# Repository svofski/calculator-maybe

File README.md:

# MK-61 and stuff

This is a collection of mildly cohesive projects related to Soviet programmable RPN calculator emulation, period-accurate displays and their decent modern imitations.

## ИЛЦ2-12/8Л module

[Standalone VFD Module](/vfdmodule)

## OLED imitation

SH1122 256x64 grayscale OLED is used to fake the VFD look. It's not the real thing, but pretty close.

A part of mk61, it is also available as a standalone minimal project/library: [vfd-imitator](https://github.com/svofski/vfd-imitator)

## MK-61

Based on [mk-61 project by sergev](https://github.com/sergev/mk-61) and [emu145 by fixelsan](https://github.com/fixelsan/emu145/). 

Runs on Pi Pico. Eventually wants to become a usable calculator with buttons and stuff. It will use either of the two displays above.

[Code here](/arduino/mk61vak)

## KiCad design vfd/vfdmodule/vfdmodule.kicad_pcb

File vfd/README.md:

# ILC2-12/8L driver module

 * Interface: SPI
 * 5V supply
 * VFD conroller PT6315

## Hardware

[KiCad project](/vfd/vfdmodule) 

[view in KiCanvas](https://kicanvas.org/?github=https%3A%2F%2Fgithub.com%2Fsvofski%2Fcalculator-maybe%2Ftree%2Fmaster%2Fvfd%2Fvfdmodule)

## Firmware

Soon

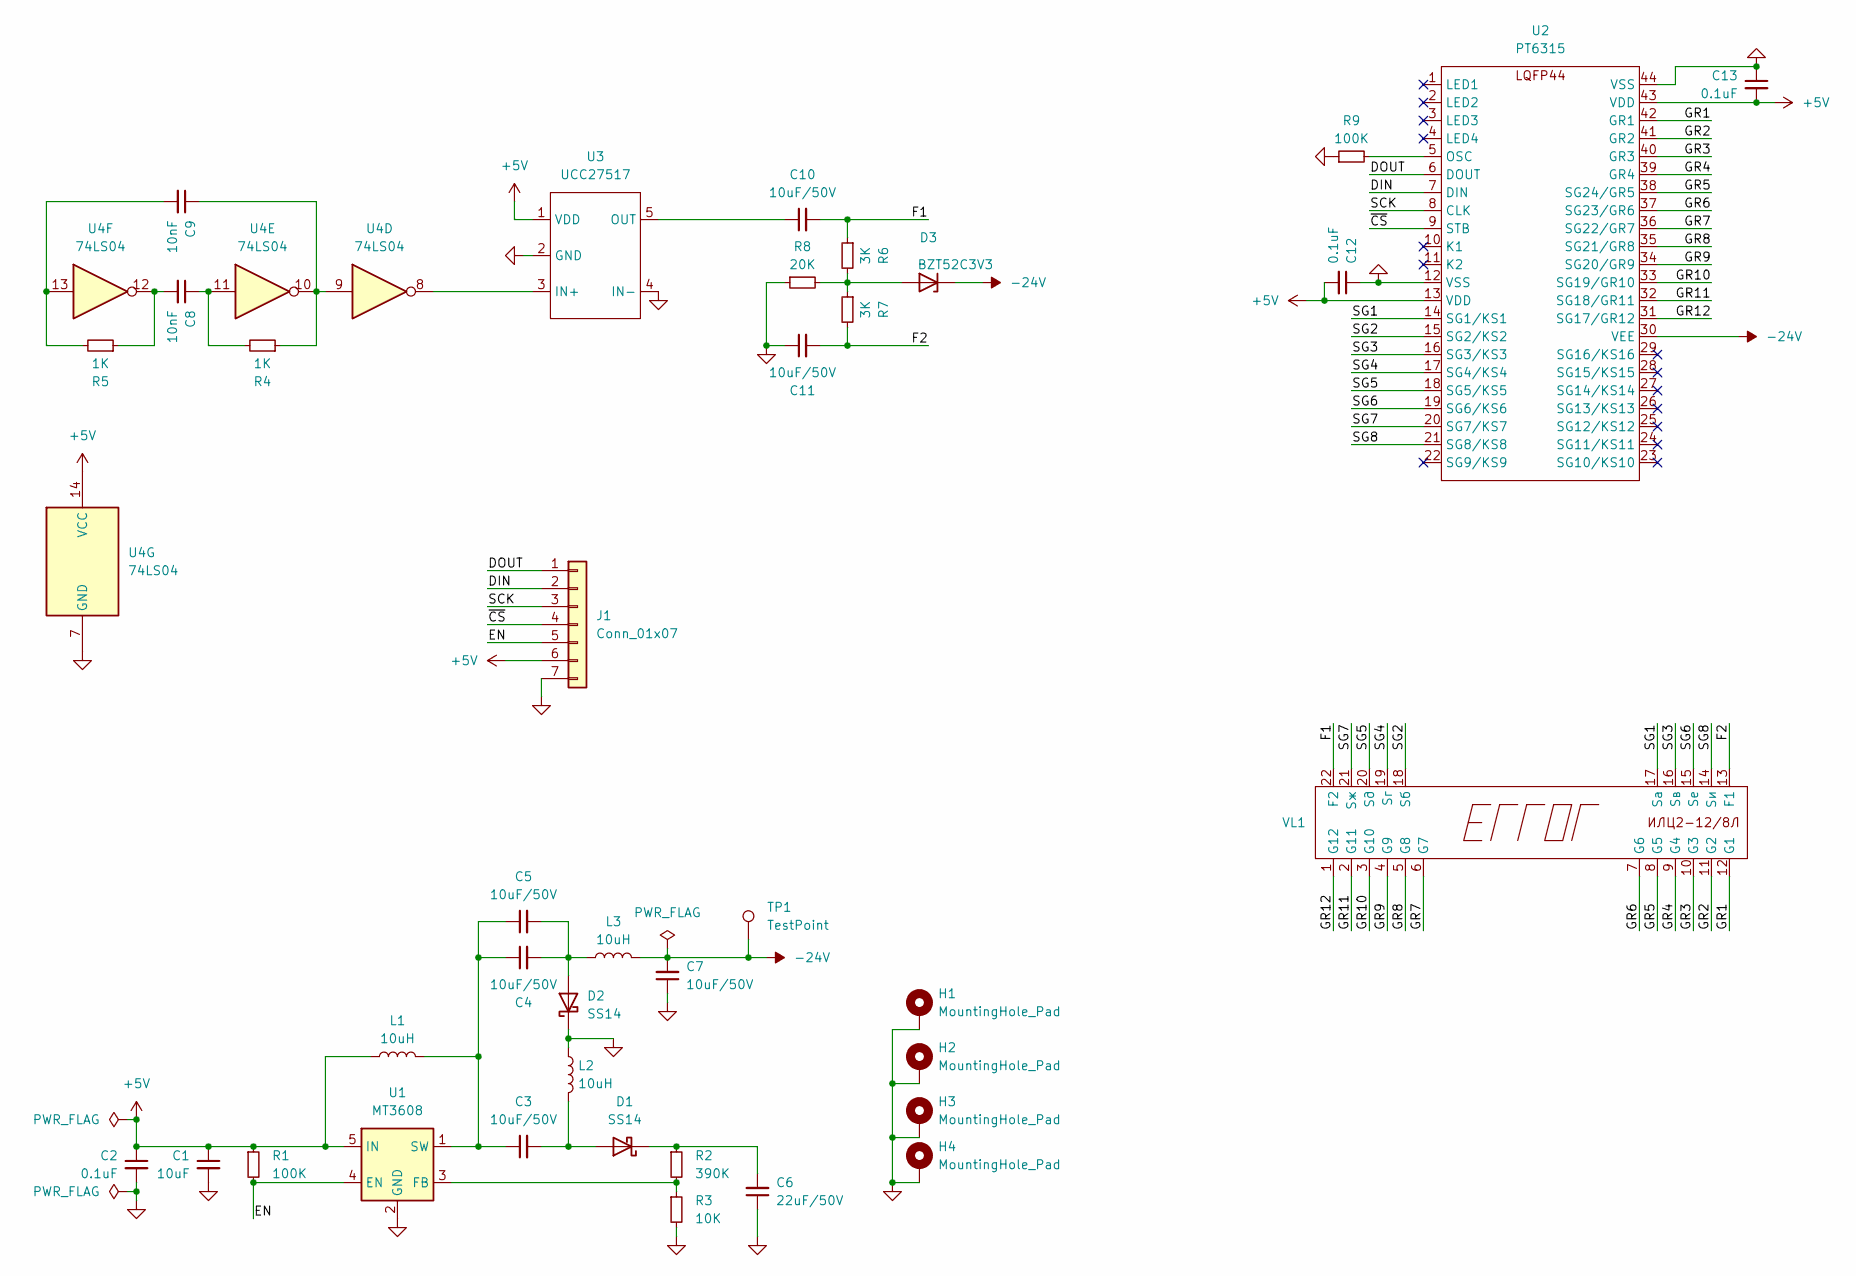
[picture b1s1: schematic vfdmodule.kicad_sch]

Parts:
C1: 10uF; C_0805_2012Metric
C2, C12, C13: 0.1uF; C_0805_2012Metric
C3, C4, C5, C7, C10, C11: 10uF/50V; C_1210_3225Metric
C6: 22uF/50V; C_1210_3225Metric
C8, C9: 10nF; C_0805_2012Metric
D1, D2: SS14; D_SMA
D3: BZT52C3V3; D_SOD-123F
H1, H2, H3, H4: MountingHole_Pad; MountingHole_2.5mm_Pad
J1: Conn_01x07; PinHeader_1x07_P2.54mm_Vertical
L1: 10uH; CD32_3.0x3.5mm
L2, L3: 10uH; L_0805_2012Metric
R1, R9: 100K; R_0805_2012Metric
R2: 390K; R_0805_2012Metric
R3: 10K; R_0805_2012Metric
R4, R5: 1K; R_0805_2012Metric
R6, R7: 3K; R_0805_2012Metric
R8: 20K; R_0805_2012Metric
TP1: TestPoint; TestPoint_THTPad_2.0x2.0mm_Drill1.0mm
U1: MT3608; SOT-23-6
U2: PT6315; LQFP-44_10x10mm_P0.8mm
U3: UCC27517; SOT-23-5
U4: 74LS04; SOIC-14_3.9x8.7mm_P1.27mm
VL1: ILC2-12_8L

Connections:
+5V: C1.1, C2.1, C12.2, C13.2, J1.6, L1.1, R1.1, U1.5 (IN), U2.13 (VDD), U2.43 (VDD), U3.1 (VDD), U4.14 (VCC)
-24V: C7.2, D3.1 (K), L3.2, TP1.1, U2.30 (VEE)
/DIN: J1.2, U2.7 (DIN)
/DOUT: J1.1, U2.6 (DOUT)
/EN: J1.5, R1.2, U1.4 (EN)
/F1: C10.2, R6.1, VL1.22 (F2)
/F2: C11.2, R7.2, VL1.13 (F1)
/GR1: U2.42 (GR1), VL1.12 (G1)
/GR2: U2.41 (GR2), VL1.11 (G2)
/GR3: U2.40 (GR3), VL1.10 (G3)
/GR4: U2.39 (GR4), VL1.9 (G4)
/GR5: U2.38 (SG24/GR5), VL1.8 (G5)
/GR6: U2.37 (SG23/GR6), VL1.7 (G6)
/GR7: U2.36 (SG22/GR7), VL1.6 (G7)
/GR8: U2.35 (SG21/GR8), VL1.5 (G8)
/GR9: U2.34 (SG20/GR9), VL1.4 (G9)
/GR10: U2.33 (SG19/GR10), VL1.3 (G10)
/GR11: U2.32 (SG18/GR11), VL1.2 (G11)
/GR12: U2.31 (SG17/GR12), VL1.1 (G12)
/SCK: J1.3, U2.8 (CLK)
/SG1: U2.14 (SG1/KS1), VL1.17 (Sа)
/SG2: U2.15 (SG2/KS2), VL1.18 (Sб)
/SG3: U2.16 (SG3/KS3), VL1.16 (Sв)
/SG4: U2.17 (SG4/KS4), VL1.19 (Sг)
/SG5: U2.18 (SG5/KS5), VL1.20 (Sд)
/SG6: U2.19 (SG6/KS6), VL1.15 (Sе)
/SG7: U2.20 (SG7/KS7), VL1.21 (Sж)
/SG8: U2.21 (SG8/KS8), VL1.14 (Sи)
/~CS: J1.4, U2.9 (STB)
GND: C1.2, C2.2, C6.1, C7.1, C11.1, C12.1, C13.1, D2.1 (K), H1.1, H2.1, H3.1, H4.1, J1.7, L2.1, R3.2, R8.1, R9.1, U1.2 (GND), U2.12 (VSS), U2.44 (VSS), U3.2 (GND), U3.4 (IN-), U4.7 (GND)
unnamed: C8.1, R4.2, U4.11
unnamed: C8.2, R5.1, U4.12
unnamed: C9.1, R4.1, U4.9, U4.10
unnamed: C9.2, R5.2, U4.13
unnamed: C3.2, D1.2 (A), L2.2
unnamed: C6.2, D1.1 (K), R2.1
unnamed: C4.2, C5.2, D2.2 (A), L3.1
unnamed: D3.2 (A), R6.2, R7.1, R8.2
unnamed: R2.2, R3.1, U1.3 (FB)
unnamed: C3.1, C4.1, C5.1, L1.2, U1.1 (SW)
unnamed: R9.2, U2.5 (OSC)
unnamed: U3.3 (IN+), U4.8
unnamed: C10.1, U3.5 (OUT)

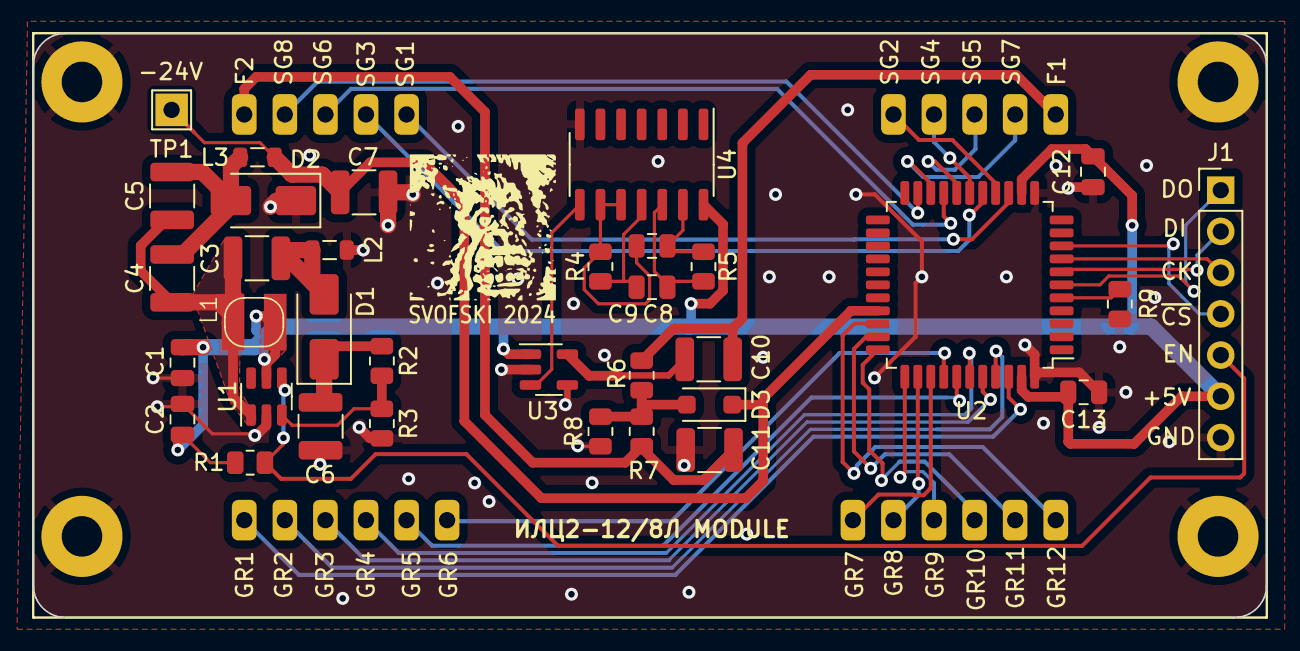
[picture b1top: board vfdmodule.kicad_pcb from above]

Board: 2 copper layers, 76.0 x 36.0 mm, 39 parts (1 on the bottom side), 43 nets.

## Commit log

2024-02-08 frist cmmit
2024-02-08 nicer blanking, ZOGS key works, pipico platform
2024-03-17 works and blinks with pretend-vfd on oled
2024-03-24 ilc2-12/8l vfd module kicad project
2024-03-25 doc files for ilc2 vfd
2024-03-25 assembled module photo
2024-03-25 moved doc
2024-03-25 fake paws
